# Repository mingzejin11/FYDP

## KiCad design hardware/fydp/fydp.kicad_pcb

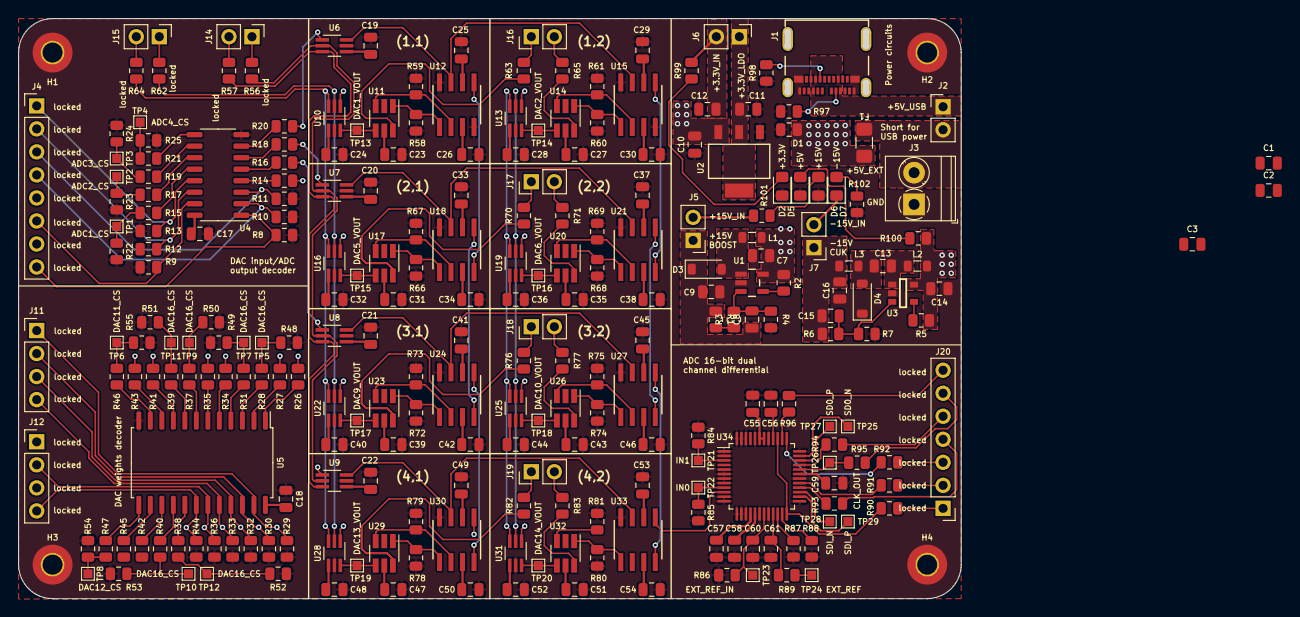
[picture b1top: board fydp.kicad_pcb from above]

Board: 2 copper layers, 104.0 x 64.0 mm, 254 parts (0 on the bottom side), 170 nets.

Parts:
C1, C2, C3: 4.7uF; C_0805_2012Metric
C7, C13, C56: 2.2uF; C_0805_2012Metric
C8: 130pF; C_0805_2012Metric
C9, C10: 10uF; C_0805_2012Metric
C11, C12, C14, C16: 22uF; C_0805_2012Metric
C15: 1nF; C_0805_2012Metric
C17, C18, C19, C20, C21, C22, C24, C25, C26, C28, C29, C30, C32, C33, C34, C36, C37, C38, C40, C41, C42, C44, C45, C46, C48, C49, C50, C52, C53, C54, C55, C57, C58, C59, C60: 0.1uF; C_0805_2012Metric
C23, C27, C31, C35, C39, C43, C47, C51: 0.01uF; C_0805_2012Metric
C61: 47uF; C_0805_2012Metric
D1: TPD1E10B06DPYR; R_0805_2012Metric
D2, D5, D6, D7: LED; LED_0805_2012Metric_Pad1.15x1.40mm_HandSolder
D3, D4: MBR0530T1G; D_SOD-123
F1: 500mA; Fuse_1206_3216Metric_Pad1.42x1.75mm_HandSolder
H1, H2, H3, H4: MountingHole_Pad; MountingHole_2.2mm_M2_Pad_TopBottom
J1: 1054500101; CONN_105450-0101_MOL
J2, J5, J6, J7, J14, J15, J16, J17, J18, J19: Conn_01x02_Pin; PinHeader_1x02_P2.54mm_Vertical
J3: Conn_01x02_Pin; TerminalBlock_Phoenix_PT-1,5-2-3.5-H_1x02_P3.50mm_Horizontal
J4: Conn_01x08_Pin; PinHeader_1x08_P2.54mm_Vertical
J11, J12: Conn_01x04_Pin; PinHeader_1x04_P2.54mm_Vertical
J20: Conn_01x07_Pin; PinHeader_1x07_P2.54mm_Vertical
L1: 10uH; L_0805_2012Metric
L2, L3: 22uH; L_0805_2012Metric
R1: 147k; R_0805_2012Metric
R2, R5, R86, R88, R89: 0; R_0805_2012Metric
R3: 1.91k; R_0805_2012Metric
R4: 13.3k; R_0805_2012Metric
R6: 40.2k; R_0805_2012Metric
R7: 3.6k; R_0805_2012Metric
R8, R9, R10, R11, R12, R13, R22, R23, R24, R25, R29, R30, R32, R33, R36, R44, R48, R49, R50, R51, R52, R53, R54, R55, R84, R85: 4.7k; R_0805_2012Metric
R14, R15, R16, R17, R18, R19, R20, R21, R26, R27, R28, R31, R34, R35, R37, R38, R39, R40, R41, R42, R43, R45, R46, R47, R56, R57, R62, R63, R64, R65, R70, R71, R76, R77, R82, R83, R90, R91, R92, R93, R94, R95, R96: 100; R_0805_2012Metric
R58, R59, R60, R61, R66, R67, R68, R69, R72, R73, R74, R75, R78, R79, R80, R81, R87: 1K; R_0805_2012Metric
R97, R98: 5.1k; R_0805_2012Metric
R99: 120; R_0805_2012Metric
R100: 290; R_0805_2012Metric
R101, R102: 1.3k; R_0805_2012Metric
TP1, TP2, TP3, TP4, TP5, TP6, TP7, TP8, TP9, TP10, TP11, TP12, TP13, TP14, TP15, TP16, TP17, TP18, TP19, TP20, TP21, TP22, TP23, TP24, TP25, TP26, TP27, TP28, TP29: TestPoint; TestPoint_Pad_1.0x1.0mm
U1: LM2733YMFX/NOPB; MF05A
U2: AZ1117IH-3.3TRG1; SOT223_AZ1117I_6P5X3P5_DIO
U3: LM2611BMF/NOPB; DBV0005A_L
U4: 74HC139N; SO-16_3.9x9.9mm_P1.27mm
U5: 74HC154D; SOP-24_7.5x15.4mm_P1.27mm
U6, U7, U8, U9, U10, U13, U16, U19, U22, U25, U28, U31: LTC2630ISC6-LZ8-TRMPBF; SOT-363_SC-70-6_Handsoldering
U11, U14, U17, U20, U23, U26, U29, U32: SN74LVC1G3157DCKR; SOT-23-6_Handsoldering
U12, U15, U18, U21, U24, U27, U30, U33: AD633ARZ-R7; R_8_ADI
U34: LTC2353ILX-16-PBF; LQFP-48_7x7mm_P0.5mm

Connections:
+3.3V: C12.1, C17.1, C18.1, C59.1, J4.5, J4.7, J6.2, J12.1, J12.3, R99.1, U4.16 (VCC), U5.24 (VCC), U34.31 (OVDD)
+5V: C1.1, C2.1, C3.1, C7.2, C10.1, C14.1, C19.1, C20.1, C21.1, C22.1, C23.1, C24.1, C27.1, C28.1, C31.1, C32.1, C35.1, C36.1, C39.1, C40.1, C43.1, C44.1, C47.1, C48.1, C51.1, C52.1, C55.1, D1.1, F1.2, L1.1, L2.1, R2.1, R5.1, R100.1, U1.5 (VIN), U2.3 (INPUT), U3.5 (VIN), U6.4 (VCC), U7.4 (VCC), U8.4 (VCC), U9.4 (VCC), U10.4 (VCC), U11.5 (VCC), U13.4 (VCC), U14.5 (VCC), U16.4 (VCC), U17.5 (VCC), U19.4 (VCC), U20.5 (VCC), U22.4 (VCC), U23.5 (VCC), U25.4 (VCC), U26.5 (VCC), U28.4 (VCC), U29.5 (VCC), U31.4 (VCC), U32.5 (VCC), U34.42 (VDD), U34.43 (VDD)
+15V: C25.1, C29.1, C33.1, C37.1, C41.1, C45.1, C49.1, C53.1, C57.1, J5.2, R101.1, U12.6 (+VS), U15.6 (+VS), U18.6 (+VS), U21.6 (+VS), U24.6 (+VS), U27.6 (+VS), U30.6 (+VS), U33.6 (+VS), U34.16 (VCC)
-15V: C26.1, C30.1, C34.1, C38.1, C42.1, C46.1, C50.1, C54.1, C58.1, D7.1 (K), J7.2, U12.3 (-VS), U15.3 (-VS), U18.3 (-VS), U21.3 (-VS), U24.3 (-VS), U27.3 (-VS), U30.3 (-VS), U33.3 (-VS), U34.17 (VEE), U34.45 (VEE)
/ADC/ADC1_BUSY_OUT_R: J20.7, R96.2
/ADC/ADC1_CS_L_R: J20.1, R90.2
/ADC/ADC1_EXTERNAL_REFIN: C60.1, R86.1, TP23.1, U34.19 (REFIN)
/ADC/ADC1_EXTERN_REF: R89.2, TP24.1
/ADC/ADC1_POWER_DOWN: R87.1, U34.22 (PD)
/ADC/ADC1_REF: C61.1, R89.1, U34.21 (REFBUF)
/ADC/ADC1_SCLK_R: J20.2, R91.2
/ADC/ADC1_SDI_R: J20.3, R92.2
/ADC/ADC1_SDO_CH0_R: J20.4, R93.2
/ADC/ADC1_SDO_CH1_R: J20.5, R94.2
/ADC/ADC1_VDDLBYP: C56.1, U34.40 (VDDLBYP)
/ADC/IN0: R85.1, TP22.1, U34.9 (IN0)
/ADC/IN1: R84.1, TP21.1, U34.3 (IN1)
/ADC/TP_ADC1_CLK_OUT_R: J20.6, R95.2
/ADC/TP_ADC1_SDI_N: TP28.1, U34.27 (SDI)
/ADC/TP_ADC1_SDI_P: TP29.1, U34.26 (SDI+)
/ADC/TP_ADC1_SDO_N: TP25.1, U34.35 (SDO)
/ADC/TP_ADC1_SDO_P: TP27.1, U34.34 (SDO+)
/ANALOG MULTIPLIER 1/DAC1_VOUT: TP13.1, U10.6 (VOUT), U11.4 (A)
/ANALOG MULTIPLIER 1/DAC2_VOUT: TP14.1, U13.6 (VOUT), U14.4 (A)
/ANALOG MULTIPLIER 1/DAC_CLK_R: J15.1, R62.2
/ANALOG MULTIPLIER 1/DAC_DATA_IN_R: J15.2, R64.2
/ANALOG MULTIPLIER 1/GPIO_SW1_POLARITY: R63.1, U11.6 (S)
/ANALOG MULTIPLIER 1/GPIO_SW1_POLARITY_R: J16.1, R63.2
/ANALOG MULTIPLIER 1/GPIO_SW2_POLARITY: R65.1, U14.6 (S)
/ANALOG MULTIPLIER 1/GPIO_SW2_POLARITY_R: J16.2, R65.2
/ANALOG MULTIPLIER 1/MULT1_Y1: R58.1, U11.1 (B2), U12.1 (Y1)
/ANALOG MULTIPLIER 1/MULT1_Y2: R59.1, U11.3 (B1), U12.2 (Y2)
/ANALOG MULTIPLIER 1/MULT2_Y1: R60.1, U14.1 (B2), U15.1 (Y1)
/ANALOG MULTIPLIER 1/MULT2_Y2: R61.1, U14.3 (B1), U15.2 (Y2)
/ANALOG MULTIPLIER 2/DAC5_VOUT: TP15.1, U16.6 (VOUT), U17.4 (A)
/ANALOG MULTIPLIER 2/DAC6_VOUT: TP16.1, U19.6 (VOUT), U20.4 (A)
/ANALOG MULTIPLIER 2/GPIO_SW5_POLARITY: R70.1, U17.6 (S)
/ANALOG MULTIPLIER 2/GPIO_SW5_POLARITY_R: J17.1, R70.2
/ANALOG MULTIPLIER 2/GPIO_SW6_POLARITY: R71.1, U20.6 (S)
/ANALOG MULTIPLIER 2/GPIO_SW6_POLARITY_R: J17.2, R71.2
/ANALOG MULTIPLIER 2/MULT5_Y1: R66.1, U17.1 (B2), U18.1 (Y1)
/ANALOG MULTIPLIER 2/MULT5_Y2: R67.1, U17.3 (B1), U18.2 (Y2)
/ANALOG MULTIPLIER 2/MULT6_Y1: R68.1, U20.1 (B2), U21.1 (Y1)
/ANALOG MULTIPLIER 2/MULT6_Y2: R69.1, U20.3 (B1), U21.2 (Y2)
/ANALOG MULTIPLIER 3/DAC9_VOUT: TP17.1, U22.6 (VOUT), U23.4 (A)
/ANALOG MULTIPLIER 3/DAC10_VOUT: TP18.1, U25.6 (VOUT), U26.4 (A)
/ANALOG MULTIPLIER 3/GPIO_SW9_POLARITY: R76.1, U23.6 (S)
/ANALOG MULTIPLIER 3/GPIO_SW9_POLARITY_R: J18.1, R76.2
/ANALOG MULTIPLIER 3/GPIO_SW10_POLARITY: R77.1, U26.6 (S)
/ANALOG MULTIPLIER 3/GPIO_SW10_POLARITY_R: J18.2, R77.2
/ANALOG MULTIPLIER 3/MULT9_Y1: R72.1, U23.1 (B2), U24.1 (Y1)
/ANALOG MULTIPLIER 3/MULT9_Y2: R73.1, U23.3 (B1), U24.2 (Y2)
/ANALOG MULTIPLIER 3/MULT10_Y1: R74.1, U26.1 (B2), U27.1 (Y1)
/ANALOG MULTIPLIER 3/MULT10_Y2: R75.1, U26.3 (B1), U27.2 (Y2)
/ANALOG MULTIPLIER 4/DAC13_VOUT: TP19.1, U28.6 (VOUT), U29.4 (A)
/ANALOG MULTIPLIER 4/DAC14_VOUT: TP20.1, U31.6 (VOUT), U32.4 (A)
/ANALOG MULTIPLIER 4/GPIO_SW13_POLARITY: R82.1, U29.6 (S)
/ANALOG MULTIPLIER 4/GPIO_SW13_POLARITY_R: J19.1, R82.2
/ANALOG MULTIPLIER 4/GPIO_SW14_POLARITY: R83.1, U32.6 (S)
/ANALOG MULTIPLIER 4/GPIO_SW14_POLARITY_R: J19.2, R83.2
/ANALOG MULTIPLIER 4/MULT13_Y1: R78.1, U29.1 (B2), U30.1 (Y1)
/ANALOG MULTIPLIER 4/MULT13_Y2: R79.1, U29.3 (B1), U30.2 (Y2)
/ANALOG MULTIPLIER 4/MULT14_Y1: R80.1, U32.1 (B2), U33.1 (Y1)
/ANALOG MULTIPLIER 4/MULT14_Y2: R81.1, U32.3 (B1), U33.2 (Y2)
/DAC INPUTS/DAC_IN_CLK_R: J14.1, R56.2
/DAC INPUTS/DAC_IN_DATA_IN_R: J14.2, R57.2
/DECODER 1/ADC1_CS_L_R: R15.1, U4.12 (2Y*0)
/DECODER 1/ADC2_CS_L_R: R17.1, U4.11 (2Y*1)
/DECODER 1/ADC3_CS_L_R: R19.1, U4.10 (2Y*2)
/DECODER 1/ADC4_CS_L_R: R21.1, U4.9 (2Y*3)
/DECODER 1/ADC_DECODER_A0: J4.2, R12.1, U4.14 (2A0)
/DECODER 1/ADC_DECODER_A1: J4.1, R13.1, U4.13 (2A1)
/DECODER 1/ADC_DECODER_EN_L: J4.6, R9.1, U4.15 (2E*)
/DECODER 1/DAC_IN1_CS_L_R: R20.2, U4.7 (1Y*3)
/DECODER 1/DAC_IN2_CS_L_R: R18.2, U4.6 (1Y*2)
/DECODER 1/DAC_IN3_CS_L_R: R16.2, U4.5 (1Y*1)
/DECODER 1/DAC_IN4_CS_L_R: R14.2, U4.4 (1Y*0)
/DECODER 1/DAC_IN_DECODER_A0: J4.4, R10.1, U4.2 (1A0)
/DECODER 1/DAC_IN_DECODER_A1: J4.3, R11.1, U4.3 (1A1)
/DECODER 1/DAC_IN_DECODER_EN_L: J4.8, R8.1, U4.1 (1E*)
/DECODER 1/TP_ADC1_CS_L: R15.2, R22.1, TP1.1
/DECODER 1/TP_ADC2_CS_L: R17.2, R23.1, TP2.1
/DECODER 1/TP_ADC3_CS_L: R19.2, R24.1, TP3.1
/DECODER 1/TP_ADC4_CS_L: R21.2, R25.1, TP4.1
/DECODER 2/DAC1_CS_L_R: R26.1, U5.1 (Y0*)
/DECODER 2/DAC2_CS_L_R: R27.1, U5.2 (Y1*)
/DECODER 2/DAC3_CS_L: R28.2, R48.1, TP5.1
/DECODER 2/DAC3_CS_L_R: R28.1, U5.3 (Y2*)
/DECODER 2/DAC4_CS_L: R31.2, R49.1, TP7.1
/DECODER 2/DAC4_CS_L_R: R31.1, U5.4 (Y3*)
/DECODER 2/DAC5_CS_L_R: R34.1, U5.5 (Y4*)
/DECODER 2/DAC6_CS_L_R: R35.1, U5.6 (Y5*)
/DECODER 2/DAC7_CS_L: R37.2, R50.1, TP9.1
/DECODER 2/DAC7_CS_L_R: R37.1, U5.7 (Y6*)
/DECODER 2/DAC8_CS_L: R39.2, R51.1, TP11.1
/DECODER 2/DAC8_CS_L_R: R39.1, U5.8 (Y7*)
/DECODER 2/DAC9_CS_L_R: R41.1, U5.9 (Y8*)
/DECODER 2/DAC10_CS_L_R: R43.1, U5.10 (Y9*)
/DECODER 2/DAC11_CS_L: R46.2, R55.1, TP6.1
/DECODER 2/DAC11_CS_L_R: R46.1, U5.11 (Y10*)
/DECODER 2/DAC12_CS_L: R47.1, R54.1, TP8.1
/DECODER 2/DAC12_CS_L_R: R47.2, U5.13 (Y11*)
/DECODER 2/DAC13_CS_L_R: R45.2, U5.14 (Y12*)
/DECODER 2/DAC14_CS_L_R: R42.2, U5.15 (Y13*)
/DECODER 2/DAC15_CS_L: R40.1, R53.1, TP10.1
/DECODER 2/DAC15_CS_L_R: R40.2, U5.16 (Y14*)
/DECODER 2/DAC16_CS_L: R38.1, R52.1, TP12.1
/DECODER 2/DAC16_CS_L_R: R38.2, U5.17 (Y15*)
/DECODER 2/DAC_DECODER_E0_L: J12.4, R44.1, U5.18 (E0*)
/DECODER 2/DAC_DECODER_E1_L: J12.2, R36.1, U5.19 (E1*)
/POWER/BOOST1_FB: C8.2, R3.2, R4.1, U1.3 (FB)
/POWER/BOOST1_FB_R: R1.2, R3.1
/POWER/BOOST1_LX: D3.2 (A), L1.2, U1.1 (SW)
/POWER/BOOST1_SHDN: R2.2, U1.4 (~SHDN)
/POWER/CUK1_FB: C15.2, R6.2, R7.1, U3.3 (NFB)
/POWER/CUK1_LX: C13.2, L2.2, U3.1 (SW)
/POWER/CUK1_LX_C: C13.1, D4.2 (A), L3.1
/POWER/CUK1_SHDN: R5.2, U3.4 (SHDN_N)
/POWER/PN15V0_CUK: C15.1, C16.1, J7.1, L3.2, R6.1
/POWER/PP3V3_LDO: C11.1, J6.1, U2.2 (OUTPUT)
/POWER/PP15V0_BOOST: C8.1, C9.1, D3.1 (K), J5.1, R1.1
/USBC RECEPTACLE/LMAO: F1.1, J2.2, J3.2
/USBC RECEPTACLE/PP5V0_USBC: J1.A4, J1.A9, J1.B4, J1.B9, J2.1
ADC1_BUSY_OUT: R96.1, U34.38 (BUSY)
ADC1_CS_L: R90.1, U34.24 (CNV), U34.39 (*CS)
ADC1_SCLK: R91.1, U34.29 (SCKI/SCKI)
ADC1_SDI: R92.1, U34.37 (SDI)
ADC1_SDO_CH0: R93.1, U34.28 (SCKI+/SDO0)
ADC1_SDO_CH1: R94.1, U34.33 (SCKO/SDO1)
DAC1_CS_L: R26.2, U10.1 (*CS/LD)
DAC2_CS_L: R27.2, U13.1 (*CS/LD)
DAC5_CS_L: R34.2, U16.1 (*CS/LD)
DAC6_CS_L: R35.2, U19.1 (*CS/LD)
DAC9_CS_L: R41.2, U22.1 (*CS/LD)
DAC10_CS_L: R43.2, U25.1 (*CS/LD)
DAC13_CS_L: R45.1, U28.1 (*CS/LD)
DAC14_CS_L: R42.1, U31.1 (*CS/LD)
DAC_CLK: R62.1, U10.2 (SCK), U13.2 (SCK), U16.2 (SCK), U19.2 (SCK), U22.2 (SCK), U25.2 (SCK), U28.2 (SCK), U31.2 (SCK)
DAC_DATA_IN: R64.1, U10.3 (SDI), U13.3 (SDI), U16.3 (SDI), U19.3 (SDI), U22.3 (SDI), U25.3 (SDI), U28.3 (SDI), U31.3 (SDI)
DAC_DECODER_A0: J11.1, R29.1, U5.23 (A0)
DAC_DECODER_A1: J11.2, R30.1, U5.22 (A1)
DAC_DECODER_A2: J11.3, R32.1, U5.21 (A2)
DAC_DECODER_A3: J11.4, R33.1, U5.20 (A3)
DAC_IN1_CS_L: R20.1, U6.1 (*CS/LD)
DAC_IN2_CS_L: R18.1, U7.1 (*CS/LD)
DAC_IN3_CS_L: R16.1, U8.1 (*CS/LD)
DAC_IN4_CS_L: R14.1, U9.1 (*CS/LD)
DAC_IN_CLK: R56.1, U6.2 (SCK), U7.2 (SCK), U8.2 (SCK), U9.2 (SCK)
DAC_IN_DATA_IN: R57.1, U6.3 (SDI), U7.3 (SDI), U8.3 (SDI), U9.3 (SDI)
GND: C1.2, C2.2, C3.2, C7.1, C9.2, C10.2, C11.2, C12.2, C14.2, C16.2, C17.2, C18.2, C19.2, C20.2, C21.2, C22.2, C23.2, C24.2, C25.2, C26.2, C27.2, C28.2, C29.2, C30.2, C31.2, C32.2, C33.2, C34.2, C35.2, C36.2, C37.2, C38.2, C39.2, C40.2, C41.2, C42.2, C43.2, C44.2, C45.2, C46.2, C47.2, C48.2, C49.2, C50.2, C51.2, C52.2, C53.2, C54.2, C55.2, C56.2, C57.2, C58.2, C59.2, C60.2, C61.2, D1.2, D2.1 (K), D4.1 (K), D5.1 (K), D6.1 (K), H1.1, H2.1, H3.1, H4.1, J1.A1, J1.A12, J1.B1, J1.B12, J3.1, R4.2, R7.2, R8.2, R9.2, R10.2, R11.2, R12.2, R13.2, R22.2, R23.2, R24.2, R25.2, R29.2, R30.2, R32.2, R33.2, R36.2, R44.2, R48.2, R49.2, R50.2, R51.2, R52.2, R53.2, R54.2, R55.2, R58.2, R59.2, R60.2, R61.2, R66.2, R67.2, R68.2, R69.2, R72.2, R73.2, R74.2, R75.2, R78.2, R79.2, R80.2, R81.2, R84.2, R85.2, R86.2, R87.2, R88.2, R97.2, R98.2, R102.1, U1.2 (GND), U2.1 (ADJ/GND), U3.2 (GND), U4.8 (GND), U5.12 (GND), U6.5 (GND), U7.5 (GND), U8.5 (GND), U9.5 (GND), U10.5 (GND), U11.2 (GND), U12.4 (Z), U12.8 (X2), U13.5 (GND), U14.2 (GND), U15.4 (Z), U15.8 (X2), U16.5 (GND), U17.2 (GND), U18.8 (X2), U19.5 (GND), U20.2 (GND), U21.8 (X2), U22.5 (GND), U23.2 (GND), U24.8 (X2), U25.5 (GND), U26.2 (GND), U27.8 (X2), U28.5 (GND), U29.2 (GND), U30.8 (X2), U31.5 (GND), U32.2 (GND), U33.8 (X2), U34.1 (GND), U34.2 (GND), U34.5 (GND), U34.6 (GND), U34.7 (GND), U34.8 (GND), U34.11 (GND), U34.12 (GND), U34.13 (GND), U34.14 (GND), U34.15 (GND), U34.18 (GND), U34.20 (GND), U34.25 (GND), U34.30 (GND), U34.36 (GND), U34.41 (GND), U34.44 (GND), U34.46 (GND), U34.47 (GND), U34.48 (GND)
IN1: U6.6 (VOUT), U12.7 (X1), U15.7 (X1)
IN2: U7.6 (VOUT), U18.7 (X1), U21.7 (X1)
IN3: U8.6 (VOUT), U24.7 (X1), U27.7 (X1)
IN4: U9.6 (VOUT), U30.7 (X1), U33.7 (X1)
MULT1_OUT: U12.5 (W), U18.4 (Z)
MULT2_OUT: U15.5 (W), U21.4 (Z)
MULT5_OUT: U18.5 (W), U24.4 (Z)
MULT6_OUT: U21.5 (W), U27.4 (Z)
MULT9_OUT: U24.5 (W), U30.4 (Z)
MULT10_OUT: U27.5 (W), U33.4 (Z)
MULT13_OUT: U30.5 (W), U34.4 (IN1+)
MULT14_OUT: U33.5 (W), U34.10 (IN0+)
unnamed: D2.2 (A), R99.2
unnamed: D5.2 (A), R100.2
unnamed: D6.2 (A), R101.2
unnamed: D7.2 (A), R102.2
unnamed: J1.A5, R97.1
unnamed: J1.B5, R98.1
unnamed: R88.1, U34.23 (LVDS/*CMOS)
TP_ADC1_CLK_OUT: R95.1, TP26.1, U34.32 (SCKO+/SCKO)

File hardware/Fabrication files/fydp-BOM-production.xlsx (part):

Date: |  |  | 45328.909722222219
Tool: |  |  | Eeschema 7.0.9
Component Count: |  |  | 258
Item | Qty | Reference(s) | Value | DNP | Footprint | LCSC | MPN | Comment | Datasheet
1 | 3 | C1, C2, C3 | 4.7uF |  | Capacitor_SMD:C_0805_2012Metric | C354262 | CC0805KKX7R8BB475 | 4.7 µF ±10% 25V Ceramic Capacitor X7R 0805 (2012 Metric) | https://www.yageo.com/upload/media/product/app/datasheet/mlc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
2 | 3 | C7, C13, C56 | 2.2uF |  | Capacitor_SMD:C_0805_2012Metric | C277470 | CC0805KKX7R8BB225 | 2.2 µF ±10% 25V Ceramic Capacitor X7R 0805 (2012 Metric) | https://www.yageo.com/upload/media/product/app/datasheet/mlc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
3 | 1 | C8 | 130pF |  | Capacitor_SMD:C_0805_2012Metric | C520003 | CC0805JRNPO9BN131 | 130 pF ±5% 50V Ceramic Capacitor C0G, NP0 0805 (2012 Metric) | https://www.yageo.com/upload/media/product/productsearch/dat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
4 | 2 | C9, C10 | 10uF |  | Capacitor_SMD:C_0805_2012Metric | C89831 | CC0805KKX5R8BB106 | 10 µF ±10% 25V Ceramic Capacitor X5R 0805 (2012 Metric) | https://www.yageo.com/upload/media/product/app/datasheet/mlc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
5 | 4 | C11, C12, C14, C16 | 22uF |  | Capacitor_SMD:C_0805_2012Metric | C784585 | CC0805MKX5R8BB226 | 22 µF ±20% 25V Ceramic Capacitor X5R 0805 (2012 Metric) | https://www.yageo.com/upload/media/product/app/datasheet/mlc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
6 | 1 | C15 | 1nF |  | Capacitor_SMD:C_0805_2012Metric | C94121 | CC0805KRX7R9BB102 | 1000 pF ±10% 50V Ceramic Capacitor X7R 0805 (2012 Metric) | https://www.yageo.com/upload/media/product/app/datasheet/mlc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
7 | 35 | C17, C18, C19, C20, C21, C22, C24, C25, C26, C28, C29, C30, C32, C33, C34, C36,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 | 0.1uF |  | Capacitor_SMD:C_0805_2012Metric | C49678 | CC0805KRX7R9BB104 | 0.1 µF ±10% 50V Ceramic Capacitor X7R 0805 (2012 Metric) | https://www.yageo.com/upload/media/product/app/datasheet/mlc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
8 | 8 | C23, C27, C31, C35, C39, C43, C47, C51 | 0.01uF |  | Capacitor_SMD:C_0805_2012Metric | C83170 | CC0805KRX7R9BB103 | 10000 pF ±10% 50V Ceramic Capacitor X7R 0805 (2012 Metric) | https://www.yageo.com/upload/media/product/app/datasheet/mlc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
9 | 1 | C61 | 47uF |  | Capacitor_SMD:C_0805_2012Metric | C109461 | CC0805MKX5R5BB476 | 47 µF ±20% 6.3V Ceramic Capacitor X5R 0805 (2012 Metric) | https://www.yageo.com/upload/media/product/app/datasheet/mlc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
10 | 1 | D1 | CDSOD323-T05 |  | Diode_SMD:D_SOD-323_HandSoldering | C3706224 | CDSOD323-T05 | 18.3V (Typ) Clamp 17A (8/20µs) Ipp Tvs Diode Surface Mount SOD-323 | https://www.bourns.com/docs/Product-Datasheets/CDSOD323-TxxC.PDF
11 | 4 | D2, D5, D6, D7 | LED |  | LED_SMD:LED_0805_2012Metric_Pad1.15x1.40mm_HandSolder | C125090 | LTST-C170GKT | Green 569nm LED Indication - Discrete 2.1V 0805 (2012 Metric) | https://mm.digikey.com/Volume0/opasdata/d220001/medias/docus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
12 | 2 | D3, D4 | MBR0530T1G |  | Diode_SMD:D_SOD-123 | C82046 | MBR0530T1G | Diode 30 V 500mA Surface Mount SOD-123 | https://www.onsemi.com/pdf/datasheet/mbr0530t1-d.pdf
13 | 1 | F1 | 500mA |  | Fuse:Fuse_1206_3216Metric_Pad1.42x1.75mm_HandSolder | C206953 | 0437.500WR | 500 mA 63 V AC 63 V DC Fuse Board Mount (Cartridge Style Excluded) Surface Moun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 | https://www.littelfuse.com/~/media/electronics/datasheets/fu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
14 | 1 | J1 | 1054500101 |  | fydp:CONN_105450-0101_MOL | C134092 | 1054500101 | USB-C (USB TYPE-C) USB 3.2 Gen 2 (USB 3.1 Gen 2, Superspeed + (USB 3.1)) Recept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 | https://tools.molex.com/pdm_docs/ps/PS-105448-001.pdf
15 | 1 | J3 | 1751248 |  | TerminalBlock_Phoenix:TerminalBlock_Phoenix_PT-1,5-2-3.5-H_1x02_P3.50mm_Horizon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 | C89122 | 1751248 | 2 Position Wire to Board Terminal Block Horizontal with Board 0.138" (3.50mm) T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 | https://mm.digikey.com/Volume0/opasdata/d220001/medias/docus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
16 | 4 | J8, J9, J10, J13 | 5011 |  | 5011:CONN1_5011_KEY | C238127 | 5011 | Black PC Test Point, Multipurpose Phosphor Bronze Silver Plating Through Hole M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 | https://www.keyelco.com/userAssets/file/M65p56.pdf
17 | 1 | L1 | 10uH |  | Inductor_SMD:L_0805_2012Metric | C162582 | LQM21FN100M80L | 10 µH Shielded Multilayer Inductor 100 mA 390mOhm Max 0805 (2012 Metric) | https://search.murata.co.jp/Ceramy/image/img/P02/JELF243B-0017.pdf
18 | 2 | L2, L3 | 22uH |  | Inductor_SMD:L_0805_2012Metric | C88185 | MLZ2012P220WT000 | 22 µH Shielded Multilayer Inductor 220 mA 1.25Ohm 0805 (2012 Metric) | https://product.tdk.com/en/system/files?file=dam/doc/product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
19 | 1 | R1 | 147k |  | Resistor_SMD:R_0805_2012Metric | C483012 | RC0805FR-07147KL | 147 kOhms ±1% 0.125W, 1/8W Chip Resistor 0805 (2012 Metric) Moisture Resistant 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 | https://www.yageo.com/upload/media/product/products/datashee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
20 | 3 | R2, R5, R88 | 0 |  | Resistor_SMD:R_0805_2012Metric | C96345 | RC0805JR-070RL | 0 Ohms Jumper Chip Resistor 0805 (2012 Metric) Moisture Resistant Thick Film | https://www.yageo.com/upload/media/product/products/datashee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
21 | 1 | R3 | 1.91k |  | Resistor_SMD:R_0805_2012Metric | C865276 | RT0805BRD071K91L | 1.91 kOhms ±0.1% 0.125W, 1/8W Chip Resistor 0805 (2012 Metric) Thin Film | https://www.yageo.com/upload/media/product/app/datasheet/rch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
22 | 1 | R4 | 13.3k |  | Resistor_SMD:R_0805_2012Metric | C274912 | RC0805FR-0713K3L | 13.3 kOhms ±1% 0.125W, 1/8W Chip Resistor 0805 (2012 Metric) Moisture Resistant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 | https://www.yageo.com/upload/media/product/products/datashee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
23 | 1 | R6 | 40.2k |  | Resistor_SMD:R_0805_2012Metric | C865475 | RT0805BRD0740K2L | 40.2 kOhms ±0.1% 0.125W, 1/8W Chip Resistor 0805 (2012 Metric) Thin Film | https://www.yageo.com/upload/media/product/app/datasheet/rch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
24 | 1 | R7 | 3.6k |  | Resistor_SMD:R_0805_2012Metric | C865466 | RT0805BRD073K6L | 3.6 kOhms ±0.1% 0.125W, 1/8W Chip Resistor 0805 (2012 Metric) Thin Film | https://www.yageo.com/upload/media/product/app/datasheet/rch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
25 | 26 | R8, R9, R10, R11, R12, R13, R22, R23, R24, R25, R29, R30, R32, R33, R36, R44, R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 | 4.7k |  | Resistor_SMD:R_0805_2012Metric | C60816 | RC0805FR-074K7L | 4.7 kOhms ±1% 0.125W, 1/8W Chip Resistor 0805 (2012 Metric) Moisture Resistant 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 | https://www.yageo.com/upload/media/product/products/datashee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
26 | 43 | R14, R15, R16, R17, R18, R19, R20, R21, R26, R27, R28, R31, R34, R35, R37, R38,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 | 100 |  | Resistor_SMD:R_0805_2012Metric | C105577 | RC0805FR-07100RL | 100 Ohms ±1% 0.125W, 1/8W Chip Resistor 0805 (2012 Metric) Moisture Resistant T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 | https://www.yageo.com/upload/media/product/products/datashee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
27 | 17 | R58, R59, R60, R61, R66, R67, R68, R69, R72, R73, R74, R75, R78, R79, R80, R81,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 | 1k |  | Resistor_SMD:R_0805_2012Metric | C95781 | RC0805FR-071KL | 1 kOhms ±1% 0.125W, 1/8W Chip Resistor 0805 (2012 Metric) Moisture Resistant Th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 | https://www.yageo.com/upload/media/product/products/datashee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
28 | 2 | R86, R89 | 0 | DNP | Resistor_SMD:R_0805_2012Metric | C96345 | RC0805JR-070RL | 0 Ohms Jumper Chip Resistor 0805 (2012 Metric) Moisture Resistant Thick Film | https://www.yageo.com/upload/media/product/products/datashee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
29 | 2 | R97, R98 | 5.1k |  | Resistor_SMD:R_0805_2012Metric | C865574 | RT0805BRD075K1L | 5.1 kOhms ±0.1% 0.125W, 1/8W Chip Resistor 0805 (2012 Metric) Thin Film | https://www.yageo.com/upload/media/product/app/datasheet/rch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
30 | 1 | R99 | 120 |  | Resistor_SMD:R_0805_2012Metric | C114245 | RC0805FR-07120RL | 120 Ohms ±1% 0.125W, 1/8W Chip Resistor 0805 (2012 Metric) Moisture Resistant T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 | https://www.yageo.com/upload/media/product/products/datashee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
31 | 1 | R100 | 290 |  | Resistor_SMD:R_0805_2012Metric | C273919 | RC0805FR-07294RL | 294 Ohms ±1% 0.125W, 1/8W Chip Resistor 0805 (2012 Metric) Moisture Resistant T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 | https://www.yageo.com/upload/media/product/products/datashee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
32 | 2 | R101, R102 | 1.3k |  | Resistor_SMD:R_0805_2012Metric | C137582 | RC0805FR-071K3L | 1.3 kOhms ±1% 0.125W, 1/8W Chip Resistor 0805 (2012 Metric) Moisture Resistant 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 | https://www.yageo.com/upload/media/product/products/datashee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
33 | 1 | U1 | LM2733YMFX/NOPB |  | fydp:MF05A | C527399 | LM2733YMFX/NOPB | Boost Switching Regulator IC Positive Adjustable 2.7V 1 Output 1A (Switch) SC-7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 | https://www.ti.com/general/docs/suppproductinfo.tsp?distId=1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

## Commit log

2024-01-29 Remove 2 channels of multiplier and change ADC
2024-01-29 Edit schematic titles
2024-01-29 remove caps on VDD and VEE on ADC
2024-02-01 Initial layout mostly complete, need to complete lots of routing
2024-02-01 Completed placement and silk for left and centre sections of the PCB
2024-02-01 Pushing all changes, I'm late for class
2024-02-01 Did some work in class lol
2024-02-02 Initial layout is pretty much complete, need to add power planes
2024-02-02 Finished layout
2024-02-05 Layout changes
2024-02-05 Separating clock and data
2024-02-05 forgot to save
2024-02-06 Generating fab files, still need to make BOM and pick and place
2024-02-06 Adding JLCPCB BOM notes
2024-02-06 Updating BOM some more
2024-02-07 Pushing laptop changes
2024-02-07 Fixed footprints
2024-02-07 Updated fabrication files
2024-02-07 Added BOM and pick and place files
2024-02-07 Adding renders
2024-02-07 Forgot to save again
2024-02-07 Production files completed
2024-02-07 Fixed BOM
2024-02-07 Production underway, Mingze is tired
2024-02-08 adding images
2024-03-07 Adding poster and 3D models
2024-03-07 Adding 3d models
2024-03-11 Adding case files
2024-03-11 Adding logo
2024-03-12 Adding more case files
